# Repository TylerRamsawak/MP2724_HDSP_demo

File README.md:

</img>

A board I made to play with an old HDSP-211X display commonly found in Motorola MicroTAC series of phones. The charger IC is an MP2724, featuring I2C, USB-C cc protocol, legacy DPDM port detection, OVP, timers, watchdogs, you name it. And its capable of charging at 2A with 3A FETs! I can't begin to describe how long I've looked for a charger just like this.<br>

The board consists of an RP2040 that controls the MP2724 via I2C, and controls the HDSP via a serial->parallel 74HC595.<br>

This is in the series towards rebuilding my Motorola MicroTAC phones.<br>

Check out the video! <a href="https://www.youtube.com/watch?v=8jdg8jAGuHc"> How I Make Circuit Boards at Home | MP2724 HDSP Demo</a><br>
(https://www.youtube.com/watch?v=8jdg8jAGuHc)

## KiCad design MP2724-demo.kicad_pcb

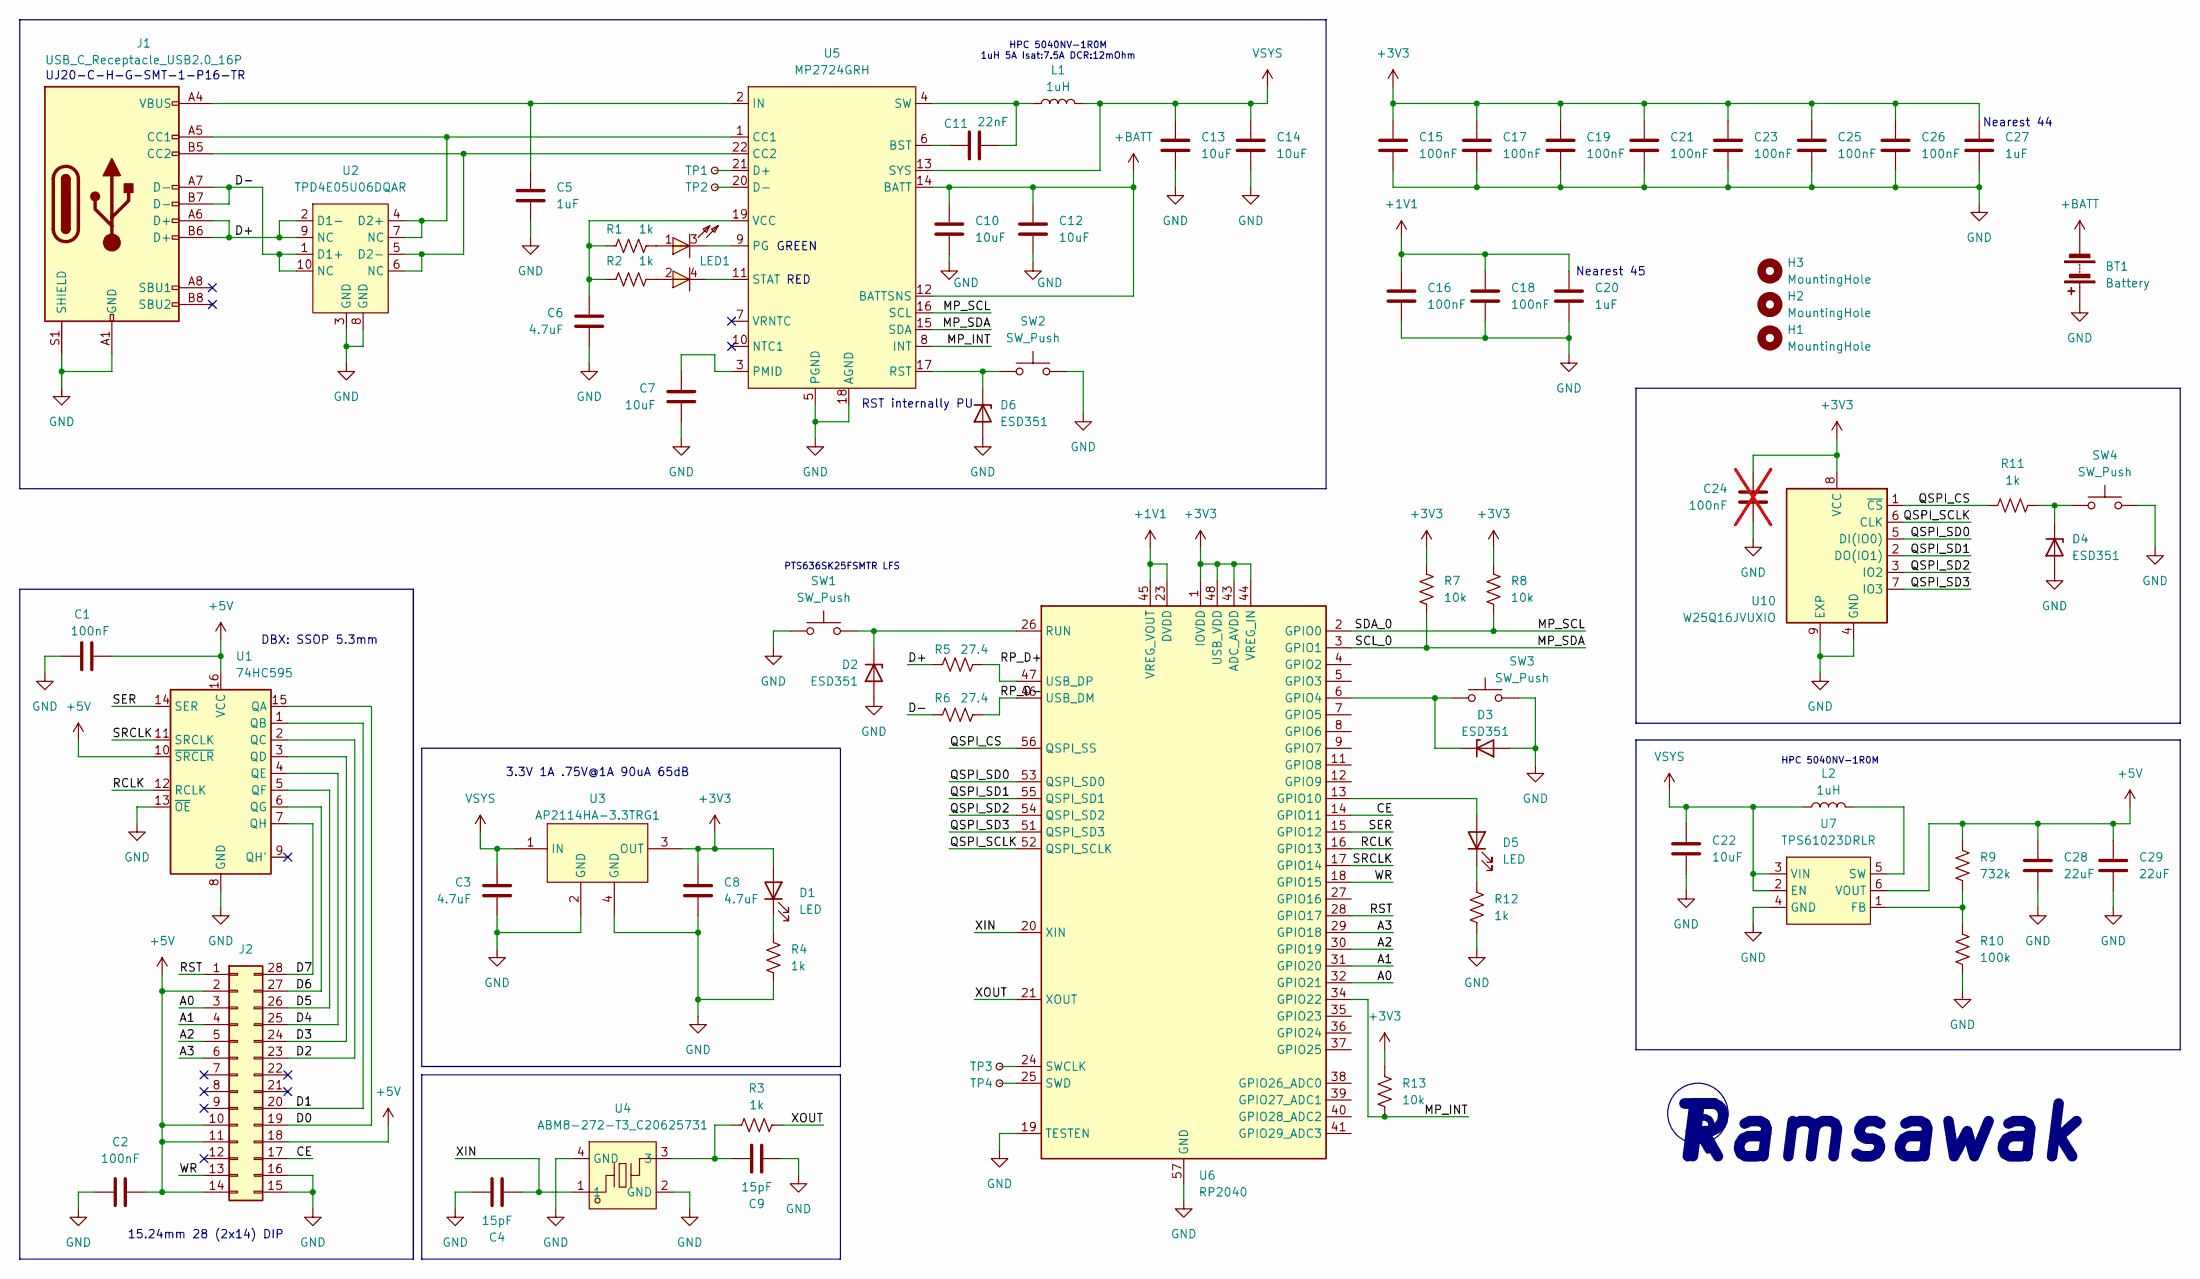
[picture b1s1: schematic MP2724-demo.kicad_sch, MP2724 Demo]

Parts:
BT1: Battery; JST_PH_S2B-PH-K_1x02_P2.00mm_Horizontal
C1, C2, C15, C16, C17, C18, C19, C21, C23, C25, C26: 100nF; C_0603_1608Metric
C3, C6, C8: 4.7uF; C_0603_1608Metric
C4, C9: 15pF; C_0603_1608Metric
C5, C20, C27: 1uF; C_0603_1608Metric
C7, C10, C12, C13, C14, C22: 10uF; C_0805_2012Metric
C11: 22nF; C_0603_1608Metric
C24: 100nF; C_0603_1608Metric; not fitted
C28, C29: 22uF; C_0603_1608Metric
D1, D5: LED; LED_0603_1608Metric
D2, D3, D4, D6: ESD351; D_0402_1005Metric
H1, H2, H3: MountingHole; MountingHole_2.2mm_M2
J1: USB_C_Receptacle_USB2.0_16P; UJ20-C-H-G-SMT-1-P16-TR
J2: Conn_02x14_Counter_Clockwise; DIP-28_W15.24mm
L1, L2: 1uH; HPC 5040NV-1R0M
LED1: LTST-C195KGJRKT; LED-ARRAY-SMD_0603-4P-L1.6-W1.5-BR-RD; LCSC Part C125104
R1, R2, R3, R4, R11, R12: 1k; R_0603_1608Metric
R5, R6: 27.4; R_0603_1608Metric
R7, R8, R13: 10k; R_0603_1608Metric
R9: 732k; R_0603_1608Metric
R10: 100k; R_0603_1608Metric
SW1, SW2, SW3, SW4: SW_Push; SW_Tactile_SPST_NO_Straight_CK_PTS636Sx25SMTRLFS
TP1, TP2, TP3, TP4: TestPoint_Small; TestPoint_Pad_D1.5mm
U1: 74HC595; SSOP-16_5.3x6.2mm_P0.65mm
U2: TPD4E05U06DQAR; USON-10_2.5x1.0mm_P0.5mm
U3: AP2114HA-3.3TRG1; SOT-223-3_L6.5-W3.4-P2.30-LS7.0-BR; LCSC Part C460314
U4: ABM8-272-T3_C20625731; CRYSTAL-SMD_4P-L3.2-W2.5-BL; LCSC Part C20625731
U5: MP2724GRH
U6: RP2040; QFN-56-1EP_7x7mm_P0.4mm_EP3.2x3.2mm
U7: TPS61023DRLR; SOT-563
U10: W25Q16JVUXIO; IC_W25Q16JVUXIQ_TR

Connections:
+1V1: C16.1, C18.1, C20.1, U6.23 (DVDD), U6.45 (VREG_VOUT), U6.50 (DVDD)
+3V3: C8.1, C15.1, C17.1, C19.1, C21.1, C23.1, C24.1, C25.1, C26.1, C27.1, D1.2 (A), R7.1, R8.1, R13.1, U3.3 (OUT), U6.1 (IOVDD), U6.10 (IOVDD), U6.22 (IOVDD), U6.33 (IOVDD), U6.42 (IOVDD), U6.43 (ADC_AVDD), U6.44 (VREG_IN), U6.48 (USB_VDD), U6.49 (IOVDD), U10.8 (VCC)
+5V: C1.1, C2.1, C28.1, C29.1, J2.2, J2.10, J2.11, J2.14, J2.18, R9.1, U1.10 (~SRCLR), U1.16 (VCC), U7.6 (VOUT)
+BATT: BT1.2 (-), C10.1, C12.1, U5.12 (BATTSNS), U5.14 (BATT)
/A0: J2.3, U6.32 (GPIO21)
/A1: J2.4, U6.31 (GPIO20)
/A2: J2.5, U6.30 (GPIO19)
/A3: J2.6, U6.29 (GPIO18)
/CE: J2.17, U6.14 (GPIO11)
/D0: J2.19, U1.15 (QA)
/D1: J2.20, U1.1 (QB)
/D2: J2.23, U1.2 (QC)
/D3: J2.24, U1.3 (QD)
/D4: J2.25, U1.4 (QE)
/D5: J2.26, U1.5 (QF)
/D6: J2.27, U1.6 (QG)
/D7: J2.28, U1.7 (QH)
/D+: J1.A6 (D+), J1.B6 (D+), R5.1, U2.2 (D1-), U2.9 (NC)
/D-: J1.A7 (D-), J1.B7 (D-), R6.1, U2.1 (D1+), U2.10 (NC)
/MP_INT: R13.2, U5.8 (INT), U6.34 (GPIO22)
/MP_SCL: R8.2, U5.16 (SCL), U6.2 (GPIO0)
/MP_SDA: R7.2, U5.15 (SDA), U6.3 (GPIO1)
/QSPI_CS: R11.1, U6.56 (QSPI_SS), U10.1 (~CS)
/QSPI_SCLK: U6.52 (QSPI_SCLK), U10.6 (CLK)
/QSPI_SD0: U6.53 (QSPI_SD0), U10.5 (DI(IO0))
/QSPI_SD1: U6.55 (QSPI_SD1), U10.2 (DO(IO1))
/QSPI_SD2: U6.54 (QSPI_SD2), U10.3 (IO2)
/QSPI_SD3: U6.51 (QSPI_SD3), U10.7 (IO3)
/RCLK: U1.12 (RCLK), U6.16 (GPIO13)
/RP_D+: R5.2, U6.47 (USB_DP)
/RP_D-: R6.2, U6.46 (USB_DM)
/RST: J2.1, U6.28 (GPIO17)
/SER: U1.14 (SER), U6.15 (GPIO12)
/SRCLK: U1.11 (SRCLK), U6.17 (GPIO14)
/WR: J2.13, U6.18 (GPIO15)
/XIN: C4.2, U4.1, U6.20 (XIN)
/XOUT: R3.2, U6.21 (XOUT)
GND: BT1.1 (+), C1.2, C2.2, C3.2, C4.1, C5.2, C6.2, C7.2, C8.2, C9.2, C10.2, C12.2, C13.2, C14.2, C15.2, C16.2, C17.2, C18.2, C19.2, C20.2, C21.2, C22.2, C23.2, C24.2, C25.2, C26.2, C27.2, C28.2, C29.2, D2.2 (A), D3.2 (A), D4.2 (A), D6.2 (A), J1.A1 (GND), J1.A12 (GND), J1.B1 (GND), J1.B12 (GND), J1.S1 (SHIELD), J2.15, J2.16, R4.2, R10.2, R12.2, SW1.2, SW2.2, SW3.2, SW4.2, U1.8 (GND), U1.13 (~OE), U2.3 (GND), U2.8 (GND), U3.2 (GND), U3.4 (GND), U4.2 (GND), U4.4 (GND), U5.5 (PGND), U5.18 (AGND), U6.19 (TESTEN), U6.57 (GND), U7.4 (GND), U10.4 (GND), U10.9 (EXP)
unnamed: C9.1, R3.1, U4.3
unnamed: D1.1 (K), R4.1
unnamed: D2.1 (K), SW1.1, U6.26 (RUN)
unnamed: D3.1 (K), SW3.1, U6.6 (GPIO4)
unnamed: D4.1 (K), R11.2, SW4.1
unnamed: D5.2 (A), U6.13 (GPIO10)
unnamed: D5.1 (K), R12.1
unnamed: D6.1 (K), SW2.1, U5.17 (RST)
unnamed: J1.A5 (CC1), U2.4 (D2+), U2.7 (NC), U5.1 (CC1)
unnamed: J1.B5 (CC2), U2.5 (D2-), U2.6 (NC), U5.22 (CC2)
unnamed: LED1.1, R1.2
unnamed: LED1.2, R2.2
unnamed: C11.1, U5.6 (BST)
unnamed: TP1.1, U5.21 (D+)
unnamed: TP2.1, U5.20 (D-)
unnamed: C5.1, J1.A4 (VBUS), J1.A9 (VBUS), J1.B4 (VBUS), J1.B9 (VBUS), U5.2 (IN)
unnamed: LED1.3, U5.9 (PG)
unnamed: C7.1, U5.3 (PMID)
unnamed: LED1.4, U5.11 (STAT)
unnamed: C11.2, L1.1, U5.4 (SW)
unnamed: C6.1, R1.1, R2.1, U5.19 (VCC)
unnamed: TP3.1, U6.24 (SWCLK)
unnamed: TP4.1, U6.25 (SWD)
unnamed: R9.2, R10.1, U7.1 (FB)
unnamed: L2.2, U7.5 (SW)
VSYS: C3.1, C13.1, C14.1, C22.1, L1.2, L2.1, U3.1 (IN), U5.13 (SYS), U7.2 (EN), U7.3 (VIN)

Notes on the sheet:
Nearest 45
HPC 5040NV-1R0M
GREEN
Ramsawak
PTS636SK25FSMTR LFS
3.3V 1A .75V@1A 90uA 65dB
UJ20-C-H-G-SMT-1-P16-TR
15.24mm 28 (2x14) DIP
Nearest 44
RED
RST internally PU
HPC 5040NV-1R0M 1uH 5A Isat:7.5A DCR:12mOhm
DBX: SSOP 5.3mm

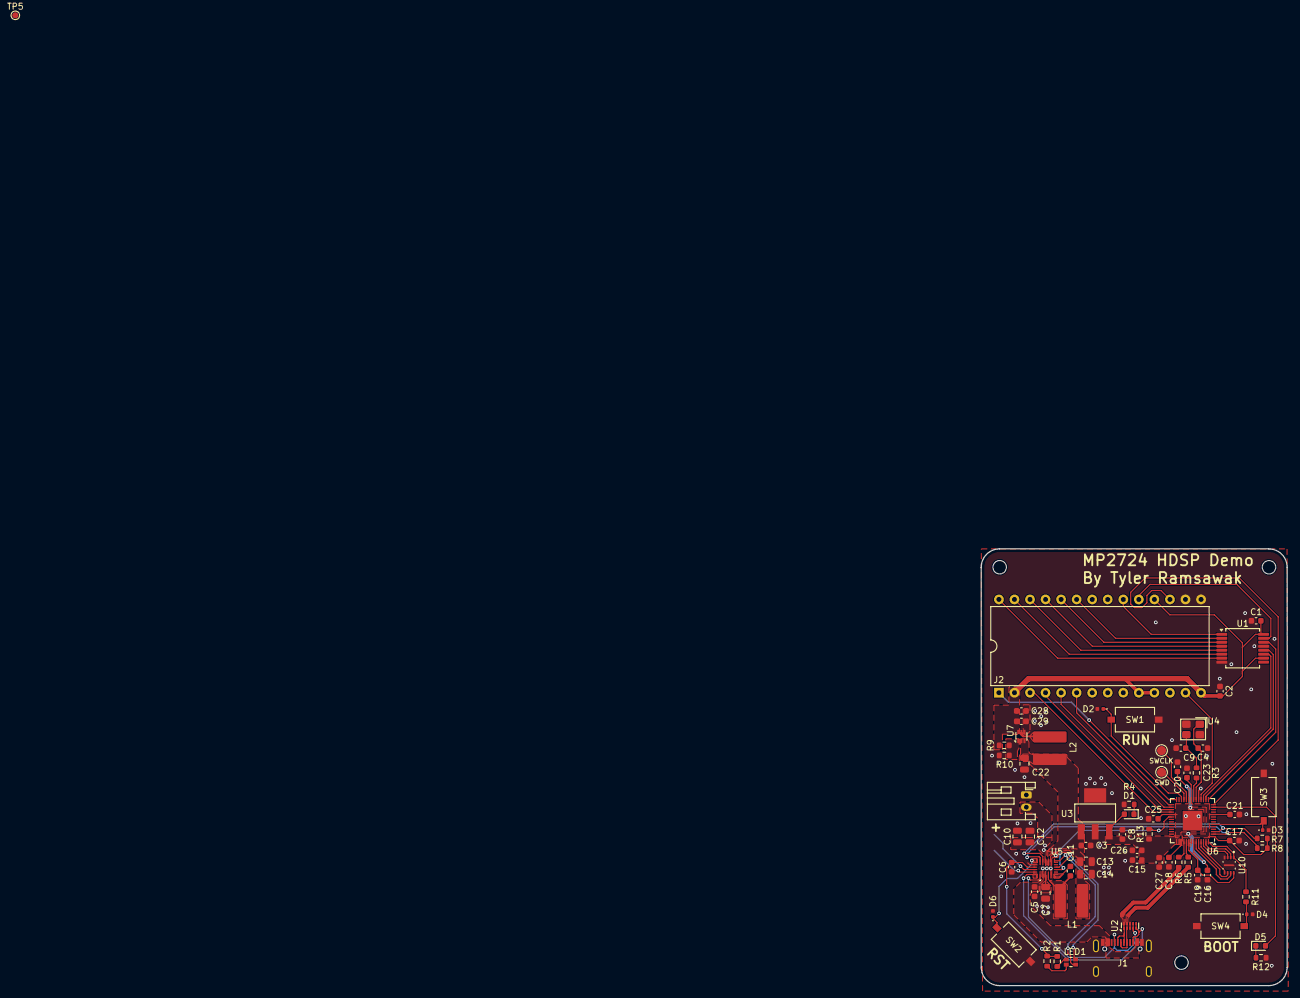
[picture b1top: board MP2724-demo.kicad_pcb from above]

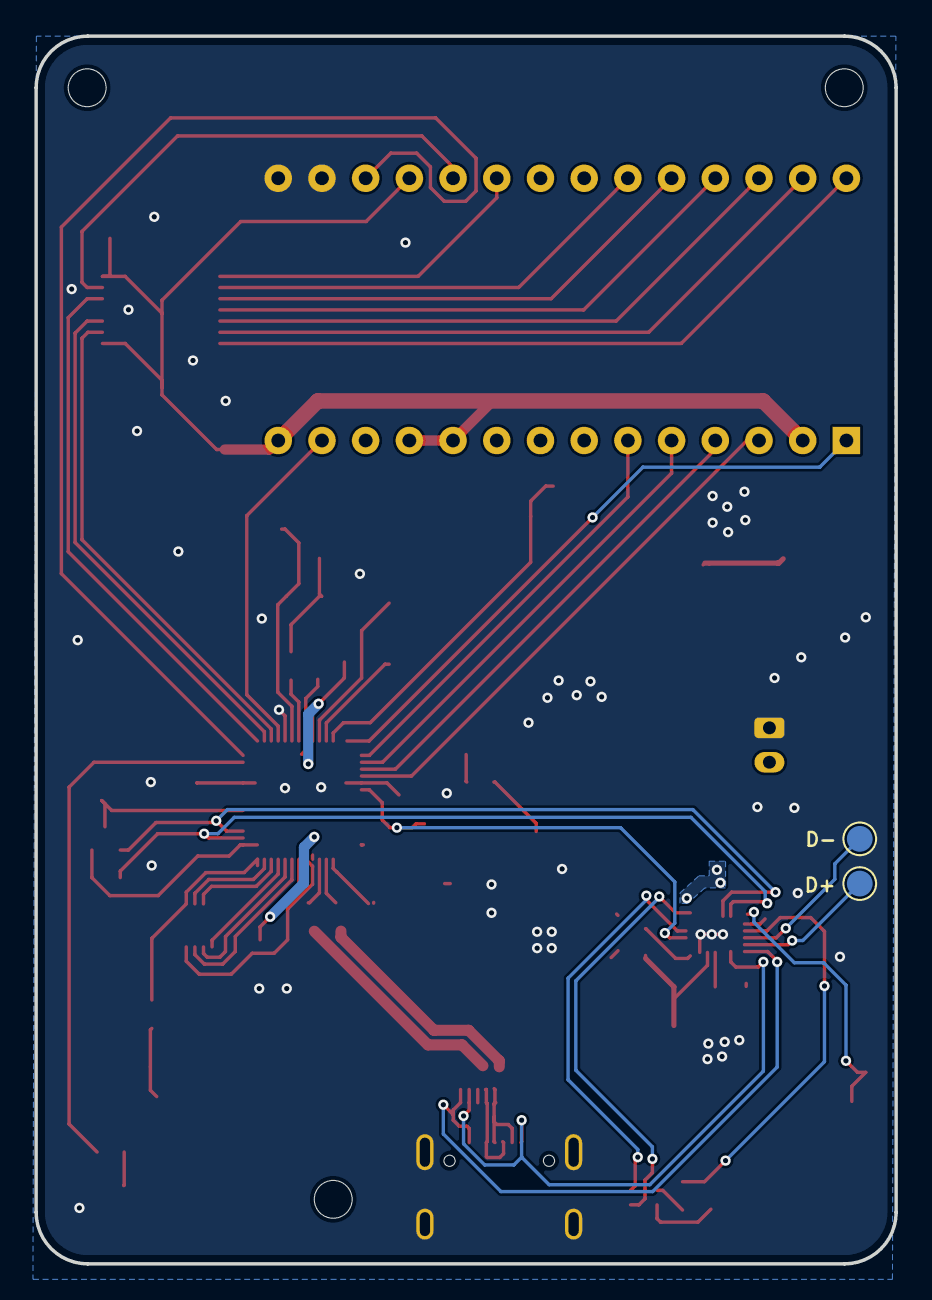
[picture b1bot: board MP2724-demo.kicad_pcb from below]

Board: 4 copper layers, 50.0 x 71.4 mm, 73 parts (2 on the bottom side), 64 nets.

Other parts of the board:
TP5: TestPoint_Small; TestPoint_Pad_D1.0mm

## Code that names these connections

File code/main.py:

from machine import Pin
from sr74hc595 import SR74HC595_BITBANG
from hdsp import HDSP_controller
import time
import utime

led = Pin(10, Pin.OUT)


#74HC595
ser = Pin(12, Pin.OUT)
rclk = Pin(13, Pin.OUT)
srclk = Pin(14, Pin.OUT)

sr = SR74HC595_BITBANG(ser, srclk, rclk)


#HDSP-2113
A0 = Pin(21, Pin.OUT)
A1 = Pin(20, Pin.OUT)
A2 = Pin(19, Pin.OUT)
A3 = Pin(18, Pin.OUT)
rst = Pin(17, Pin.OUT)
wr = Pin(15, Pin.OUT)
ce = Pin(11, Pin.OUT)

display = HDSP_controller(A0, A1, A2, A3, rst, wr, ce)

display.reset()

def update_display(time):
    char_codes = []
    for i, char in enumerate(time):
        char_code = display.get_char_code(char) #returns 18 since char='H'
        sr.bits(char_code, 8)
        sr.latch()
        position = 8-len(time)+i
        display.char_position(position)
        display.write_cycle()


hour = 14
minute = 16
second = 00

last_update = utime.time()

while True:
    current_time = utime.time()
    
    if current_time - last_update >= 1:
        elapsed = current_time - last_update
        last_update = current_time

        # Update seconds, minutes, and hours
        second += elapsed
        if second >= 60:
            minute += second // 60
            second = second % 60
        if minute >= 60:
            hour += minute // 60
            minute = minute % 60
        if hour >= 24:
            hour = hour % 24
            
        update_display(f'{hour}:{minute}:{second}')
    utime.sleep(0.1)
